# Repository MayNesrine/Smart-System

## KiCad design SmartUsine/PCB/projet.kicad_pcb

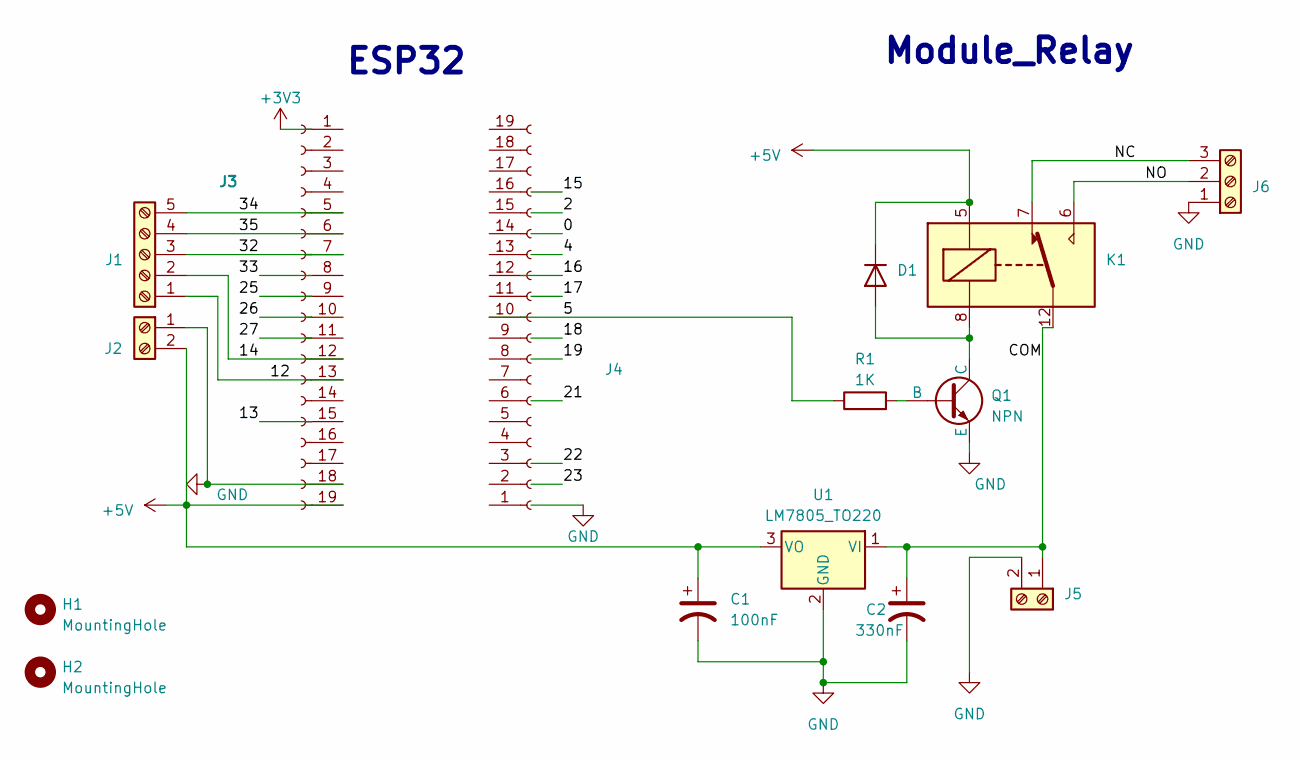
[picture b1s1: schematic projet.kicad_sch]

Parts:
C1: 100nF; C_Disc_D5.0mm_W2.5mm_P2.50mm
C2: 330nF; C_Disc_D5.0mm_W2.5mm_P2.50mm
D1: 1N4007; D_DO-41_SOD81_P7.62mm_Horizontal
H1, H2: MountingHole; MountingHole_2.5mm_Pad
J1: Screw_Terminal_01x05; PhoenixContact_MSTBVA_2,5_5-G_1x05_P5.00mm_Vertical
J2, J5: Screw_Terminal_01x02; TerminalBlock_Phoenix_MKDS-1,5-2-5.08_1x02_P5.08mm_Horizont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
J3, J4: Conn_01x19_Socket; PinSocket_1x19_P2.54mm_Vertical
J6: Screw_Terminal_01x03; PhoenixContact_MSTBVA_2,5_3-G_1x03_P5.00mm_Vertical
K1: TIANBO-HJR-4102-L; Relay_SPDT_HJR-4102
Q1: NPN; TO-92
R1: 1K; R_Axial_DIN0309_L9.0mm_D3.2mm_P12.70mm_Horizontal
U1: LM7805_TO220; TO-220-3_Vertical

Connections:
+5V: C1.1, D1.1 (K), J2.2, J3.19, K1.5, U1.3 (VO)
/5: J4.10, R1.1
/12: J1.1, J3.13
/14: J1.2, J3.12
/32: J1.3, J3.7
/34: J1.5, J3.5
/35: J1.4, J3.6
/COM: C2.1, J5.1, K1.12, U1.1 (VI)
/NC: J6.3, K1.7
/NO: J6.2, K1.6
GND: C1.2, C2.2, J2.1, J3.18, J5.2, J6.1, Q1.3 (E), U1.2 (GND)
unnamed: D1.2 (A), K1.8, Q1.1 (C)
unnamed: Q1.2 (B), R1.2

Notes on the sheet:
ESP32
Module_Relay

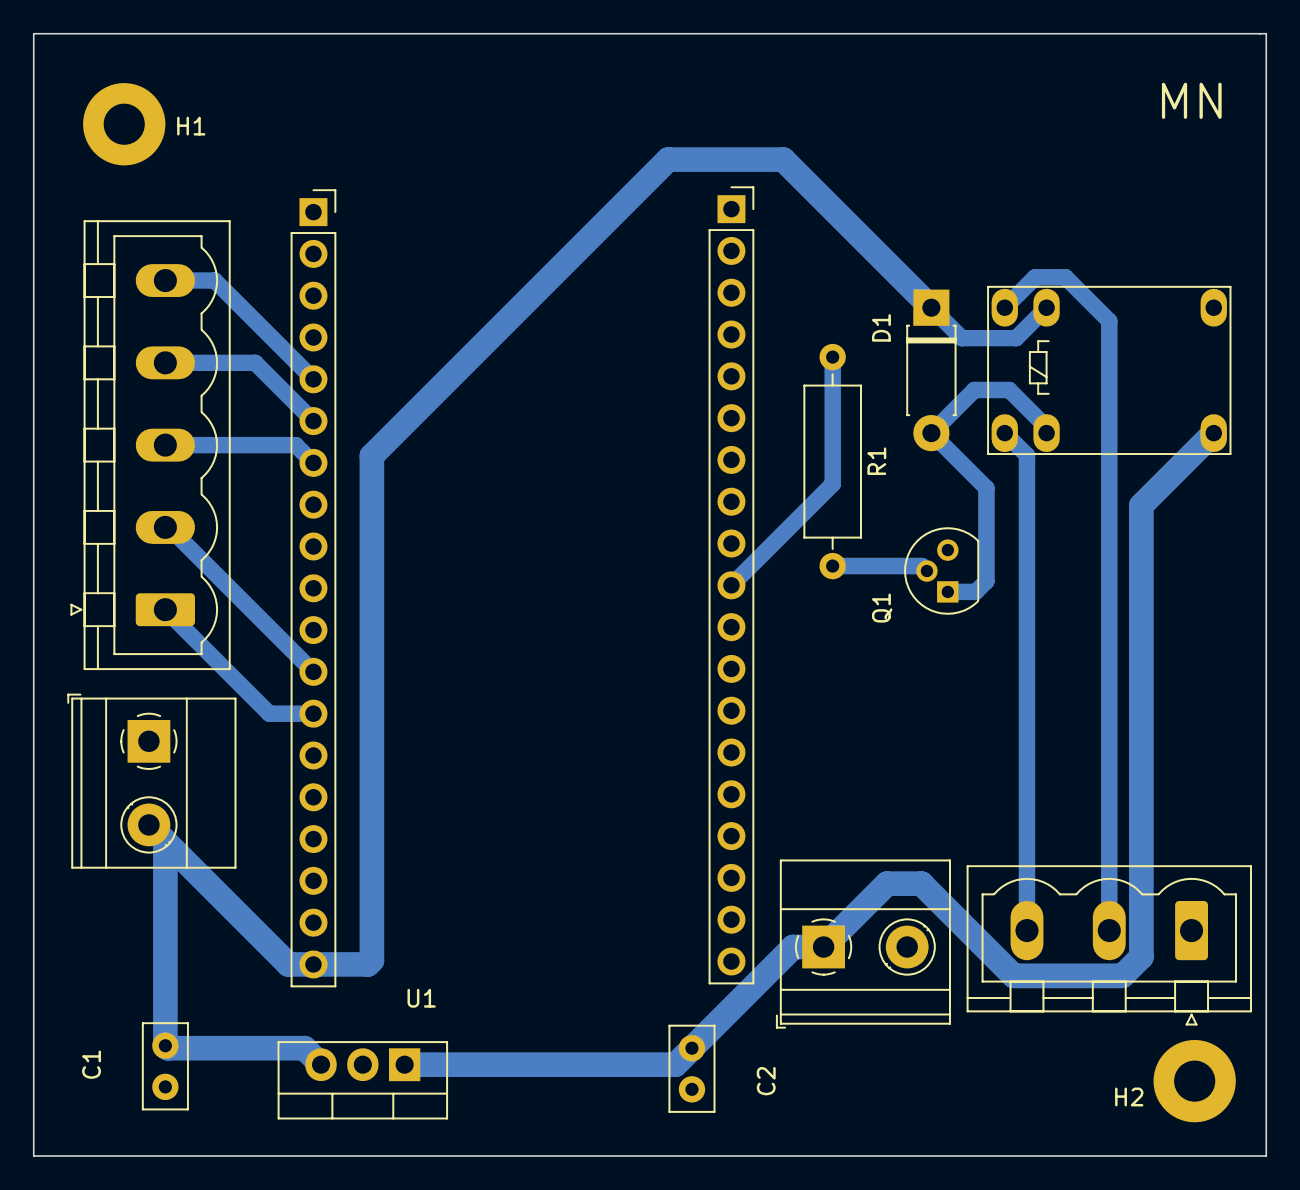
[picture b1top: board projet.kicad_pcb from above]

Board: 2 copper layers, 74.9 x 68.2 mm, 15 parts (0 on the bottom side), 13 nets.

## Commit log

2023-07-12 Smart Usine
2023-07-26 system
